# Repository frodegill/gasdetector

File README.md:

# gasdetector
Schematic and code for Arduino gas detector shield (MQ-2, MQ-7, MQ-8, MQ-9 and MQ-135)

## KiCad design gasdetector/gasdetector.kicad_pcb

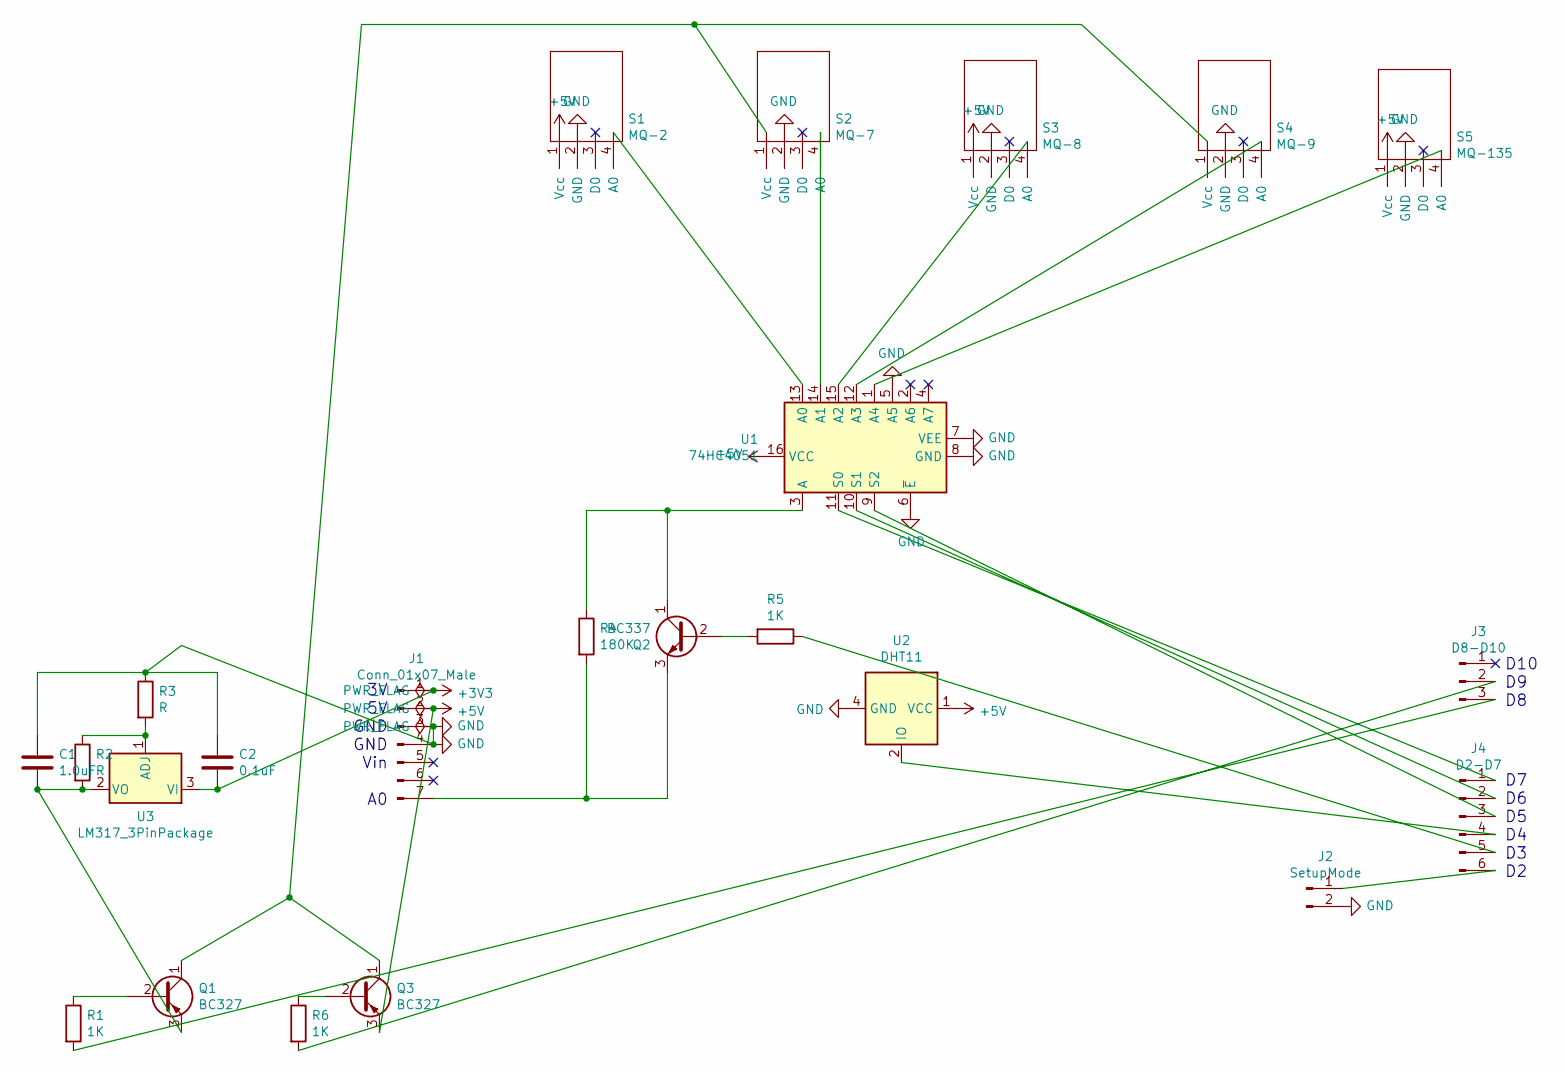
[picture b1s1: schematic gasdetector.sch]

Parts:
C1: 1.0uF; C_Radial_D8.0mm_H7.0mm_P3.50mm
C2: 0.1uF; C_Disc_D3.8mm_W2.6mm_P2.50mm
J1: Conn_01x07_Male; PinHeader_1x07_P2.54mm_Vertical
J2: SetupMode; PinHeader_1x02_P2.54mm_Vertical
J3: D8-D10; PinHeader_1x03_P2.54mm_Vertical
J4: D2-D7; PinHeader_1x06_P2.54mm_Vertical
Q1, Q3: BC327; TO-92_Inline
Q2: BC337; TO-92
R1, R5, R6: 1K; R_Axial_DIN0207_L6.3mm_D2.5mm_P10.16mm_Horizontal
R2, R3: R; R_Axial_DIN0207_L6.3mm_D2.5mm_P10.16mm_Horizontal
R4: 180K; R_Axial_DIN0207_L6.3mm_D2.5mm_P10.16mm_Horizontal
S1: MQ-2; MQ-x
S2: MQ-7; MQ-x
S3: MQ-8; MQ-x
S4: MQ-9; MQ-x
S5: MQ-135; MQ-x
U1: 74HC4051; 74HC4051N
U2: DHT11; AM2302
U3: LM317_3PinPackage; LM317

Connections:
+3V3: C2.2, J1.1, U3.3 (VI)
+5V: J1.2, Q3.3 (E), S1.1 (Vcc), S3.1 (Vcc), S5.1 (Vcc), U1.16 (VCC), U2.1 (VCC)
GND: C1.1, C2.1, J1.3, J1.4, J2.2, R3.1, S1.2 (GND), S2.2 (GND), S3.2 (GND), S4.2 (GND), S5.2 (GND), U1.5 (A5), U1.6 (~E), U1.7 (VEE), U1.8 (GND), U2.4 (GND)
unnamed: C1.2, Q1.3 (E), R2.2, U3.2 (VO)
unnamed: J1.7, Q2.3 (E), R4.2
unnamed: J2.1, J4.6
unnamed: J3.2, R6.2
unnamed: J3.3, R1.2
unnamed: J4.1, U1.11 (S0)
unnamed: J4.2, U1.10 (S1)
unnamed: J4.3, U1.9 (S2)
unnamed: J4.4, U2.2 (IO)
unnamed: J4.5, R5.1
unnamed: Q1.1 (C), Q3.1 (C), S2.1 (Vcc), S4.1 (Vcc)
unnamed: Q1.2 (B), R1.1
unnamed: Q2.1 (C), R4.1, U1.3 (A)
unnamed: Q2.2 (B), R5.2
unnamed: Q3.2 (B), R6.1
unnamed: R2.1, R3.2, U3.1 (ADJ)
unnamed: S1.4 (A0), U1.13 (A0)
unnamed: S2.4 (A0), U1.14 (A1)
unnamed: S3.4 (A0), U1.15 (A2)
unnamed: S4.4 (A0), U1.12 (A3)
unnamed: S5.4 (A0), U1.1 (A4)

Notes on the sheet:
D10 D9 D8
D7 D6 D5 D4 D3 D2
3V 5V GND GND Vin A0

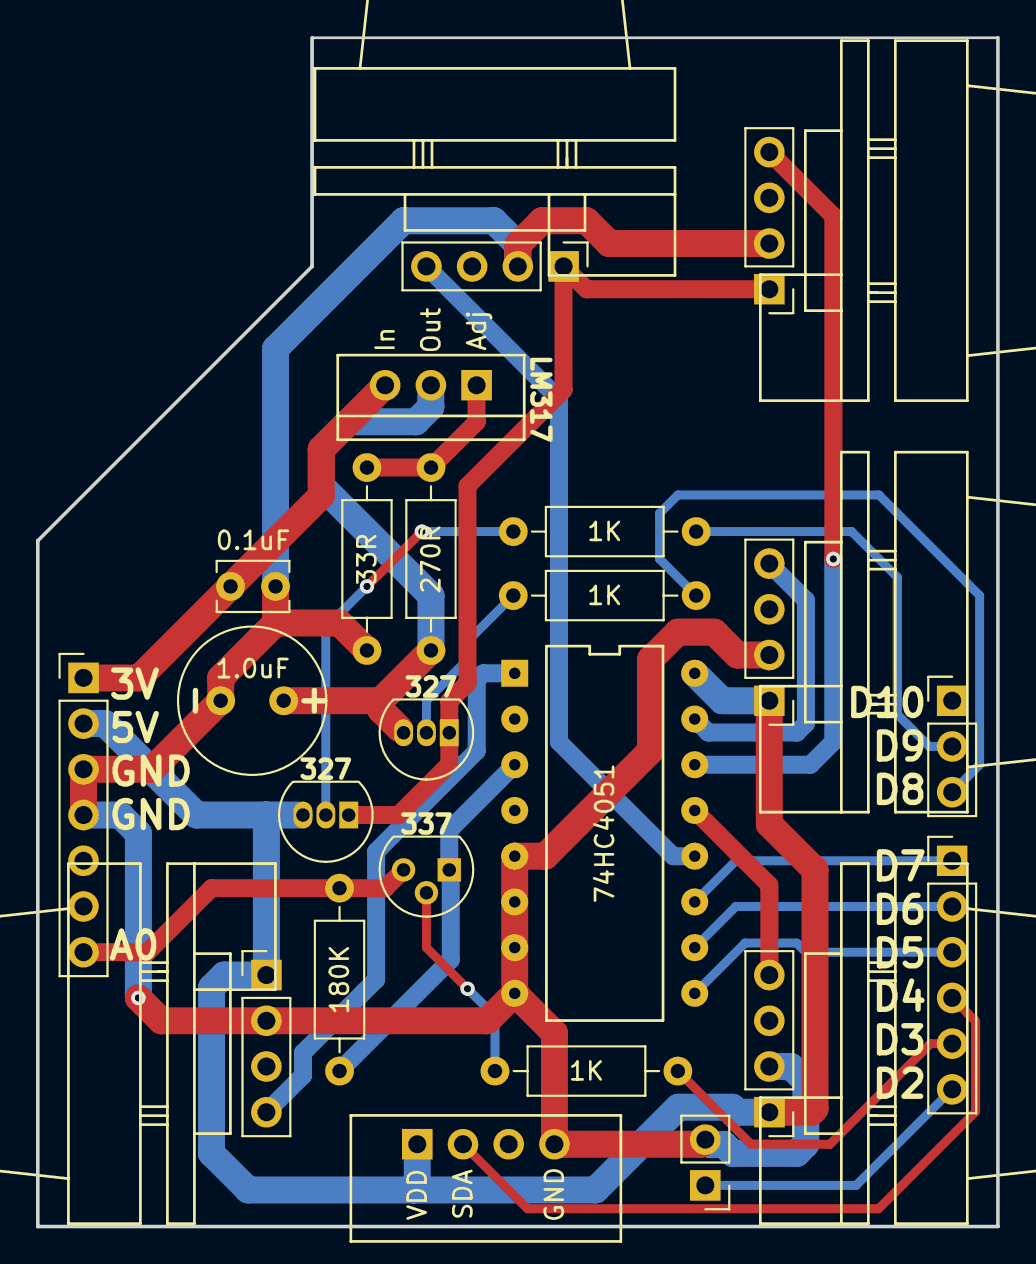
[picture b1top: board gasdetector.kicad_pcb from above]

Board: 2 copper layers, 53.3 x 66.0 mm, 23 parts (0 on the bottom side), 24 nets.

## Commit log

2019-11-28 Initial empty MQTT Arduino project
2020-01-21 Added PCB
